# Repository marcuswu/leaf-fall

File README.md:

# Leaf Fall
Leaf Fall is a 6x3+4keys column-staggered split portable folding keyboard using Ultra-Low Profile (ULP) switches which builds on the Leaf Fold to add it to the unwired family tree ([Lotus 58 unWired](https://www.reddit.com/r/ErgoMechKeyboards/comments/1h69vc7/ad_lotus_58_unwired_available_for_preorder/), [Mitosis](https://www.reddit.com/r/MechanicalKeyboards/comments/66588f/wireless_split_qmk_mitosis/), and [mikefives](https://www.reddit.com/r/ErgoMechKeyboards/comments/1qfprec/mikefives_split_incl_my_longest_writeup_ever/))

## Warning ##
This board is under active development and is not ready for builds yet. In particular, some of the models, the bill of materials, etc are not up to date.

## Introduction and Background

During the planning phase for my ULP switches, [u/dynam1keNL](https://www.reddit.com/user/dynam1keNL/) posted about his mikefives, a radical new build that was diodeless, wireless, portless, and ultra-low power due to use of the Nordic Gazell wireless protocol among other innovations.

The ultra-low power design had me entralled and I knew I had to make a version of my Leaf Fold that builds in some of those features. This became the Leaf Fall.

## Using this repository

This repository contains:

* Models for the keyboard's case in STEP format with engineering drawings
* KiCAD project for the PCB

A [bill of materials](https://docs.google.com/spreadsheets/d/1gnvod9HGQc0NwxPJ2fzenmY7mPNX9EfSASZGwRChprs/edit?gid=0#gid=0) for constructing the keyboard is also available

## Build Guide

A build guide is in the works.

## TODO

* Update the board to remove ports, power switch, reset button
* Update Case to remove holes for ports, power switch, reset button
* Remove diodes
* Design dongle
* Ensure new ULP switches work
* Build it & test it
* Create a build guide
* Update the BoM (build it into this repo so it is versioned)

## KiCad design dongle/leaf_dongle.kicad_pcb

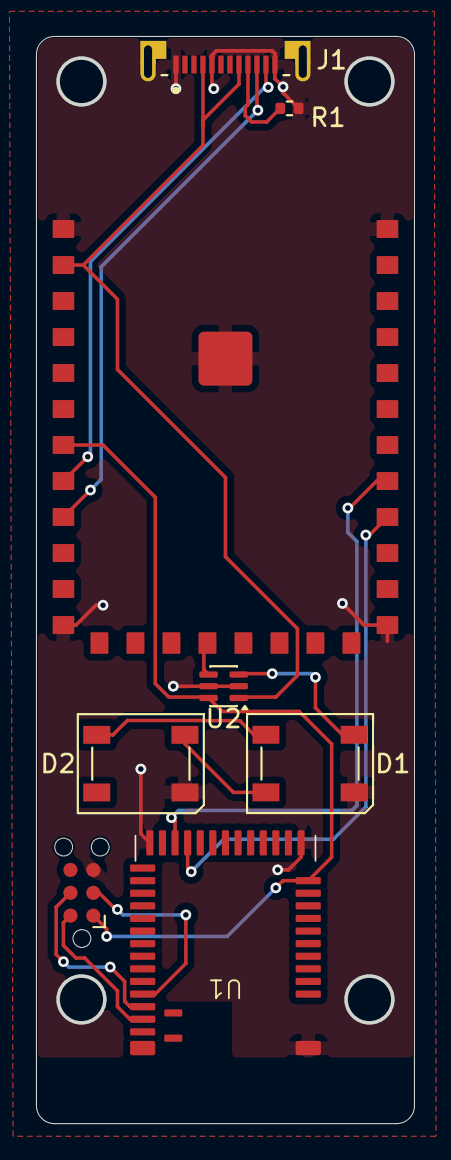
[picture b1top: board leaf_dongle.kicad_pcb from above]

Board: 2 copper layers, 20.9 x 60.3 mm, 8 parts (0 on the bottom side), 15 nets.

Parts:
1: MODULE_RP2040_SHIELD
D1, D2: SK6812; LED_SK6812_PLCC4_5.0x5.0mm_P3.2mm
J1: UP20-C-F-G-FL-P12-TR; SAMESKY_UP20-C-F-G-FL-P12-TR
J2: TC2030; Tag-Connect_TC2030-IDC-NL_2x03_P1.27mm_Vertical
R1: 5.1k; R_0402_1005Metric
U1: Raytac_MDBT42Q_P
U2: SN74LVC1T45DCK; SOT-363_SC-70-6

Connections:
-3V3: 1.7 (3V3), J2.1, U1.11 (VDD), U2.6 (VCCB)
GND: 1.1 (GND), 1.12 (GND), 1.21 (GND), 1.32 (GND), 1.33 (GND), D1.1 (VSS), D2.1 (VSS), J1.A1 (GND), J1.A12 (GND__1), J1.B12 (GND__2), J2.5, R1.2, U1.1 (GND), U1.12 (GND), U1.24 (GND), U2.2 (GND), U2.5 (DIR)
NEO: 1.16 (GP3), U2.4 (B)
unnamed: D1.2 (DIN), U2.3 (A)
unnamed: D1.4 (DOUT), D2.2 (DIN)
unnamed: D1.3 (VDD), D2.3 (VDD)
unnamed: J1.A5 (CC1), R1.1
RESET: J2.3, U1.35 (P0.21/RESET)
SWDCLK: J2.4, U1.36 (SWDCLK)
SWDIO: J2.2, U1.37 (SWDIO)
UART_RX: 1.25 (GP13), U1.22 (P0.09)
UART_TX: 1.24 (GP12), U1.21 (P0.08)
USB_D+: 1.9 (USB_D+), J1.A6 (DP1)
USB_D-: 1.8 (USB_D-), J1.A7 (DN1)
VCC: 1.2 (VIN), J1.A4 (VBUS), J1.B9 (VBUS__1), U2.1 (VCCA)

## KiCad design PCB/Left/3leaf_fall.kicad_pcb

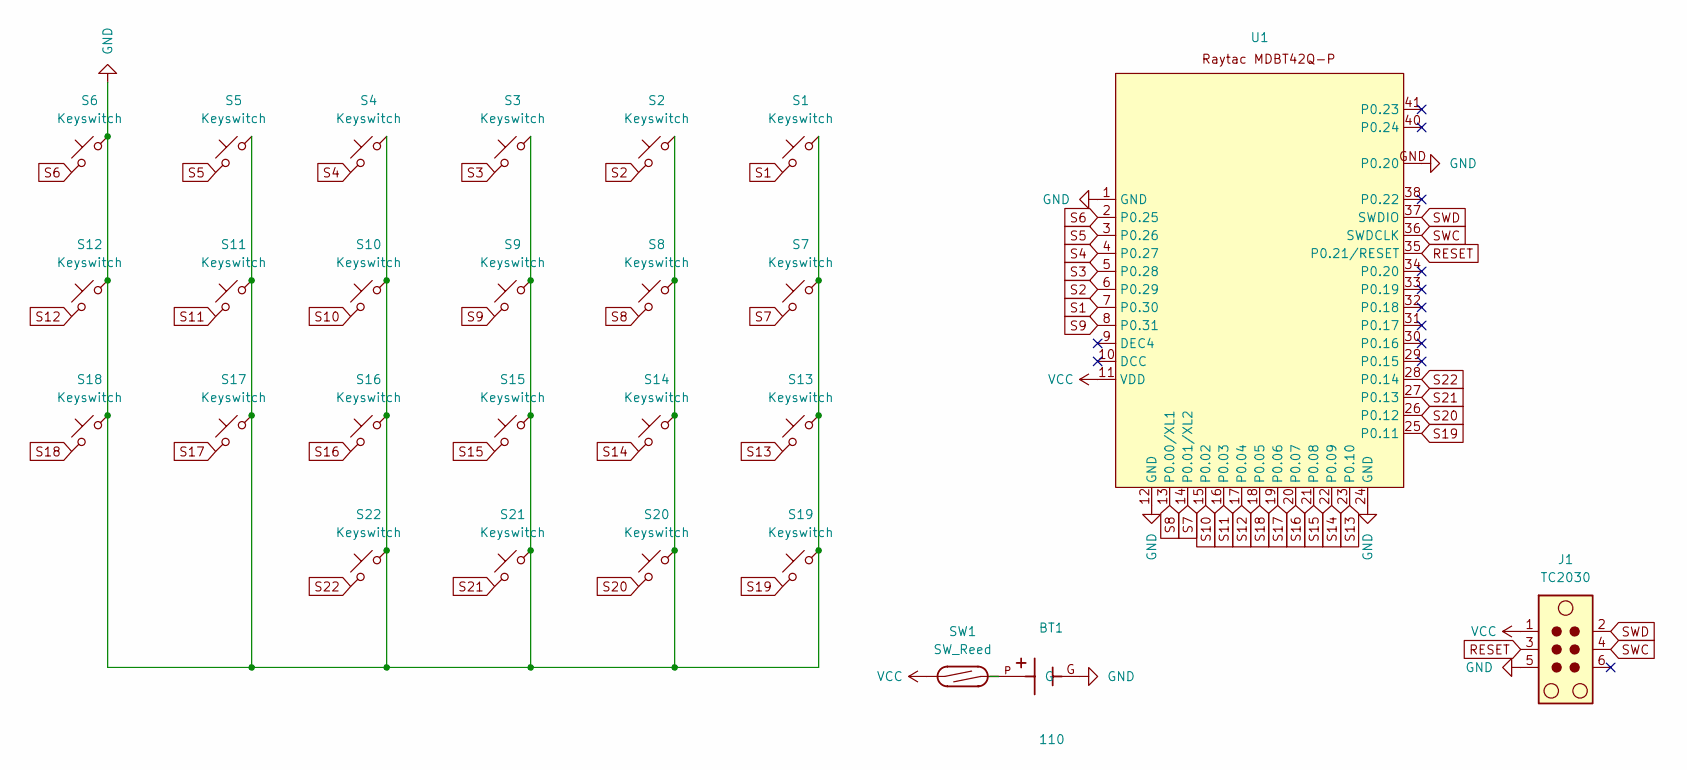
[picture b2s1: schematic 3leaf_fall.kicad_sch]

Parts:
BT1: 110; BAT_110_2032
J1: TC2030; Tag-Connect_TC2030-IDC-NL_2x03_P1.27mm_Vertical
S1, S2, S3, S4, S5, S6, S7, S8, S9, S10, S11, S12, S13, S14, S15, S16, S17, S18, S19, S20, S21, S22: Keyswitch; My_ULP_Scissor
SW1: SW_Reed; Magnet_reed_switch
U1: Raytac_MDBT42Q_P

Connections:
GND: BT1.G (G_G), J1.5, S1.1, S2.1, S3.1, S4.1, S5.1, S6.1, S7.1, S8.1, S9.1, S10.1, S11.1, S12.1, S13.1, S14.1, S15.1, S16.1, S17.1, S18.1, S19.1, S20.1, S21.1, S22.1, U1.1 (GND), U1.12 (GND), U1.24 (GND), U1.GND (P0.20)
unnamed: BT1.P, SW1.2
RESET: J1.3, U1.35 (P0.21/RESET)
S1: S1.2, U1.7 (P0.30)
S2: S2.2, U1.6 (P0.29)
S3: S3.2, U1.5 (P0.28)
S4: S4.2, U1.4 (P0.27)
S5: S5.2, U1.3 (P0.26)
S6: S6.2, U1.2 (P0.25)
S7: S7.2, U1.14 (P0.01/XL2)
S8: S8.2, U1.13 (P0.00/XL1)
S9: S9.2, U1.8 (P0.31)
S10: S10.2, U1.15 (P0.02)
S11: S11.2, U1.16 (P0.03)
S12: S12.2, U1.17 (P0.04)
S13: S13.2, U1.23 (P0.10)
S14: S14.2, U1.22 (P0.09)
S15: S15.2, U1.21 (P0.08)
S16: S16.2, U1.20 (P0.07)
S17: S17.2, U1.19 (P0.06)
S18: S18.2, U1.18 (P0.05)
S19: S19.2, U1.25 (P0.11)
S20: S20.2, U1.26 (P0.12)
S21: S21.2, U1.27 (P0.13)
S22: S22.2, U1.28 (P0.14)
SWC: J1.4, U1.36 (SWDCLK)
SWD: J1.2, U1.37 (SWDIO)
VCC: J1.1, SW1.1, U1.11 (VDD)

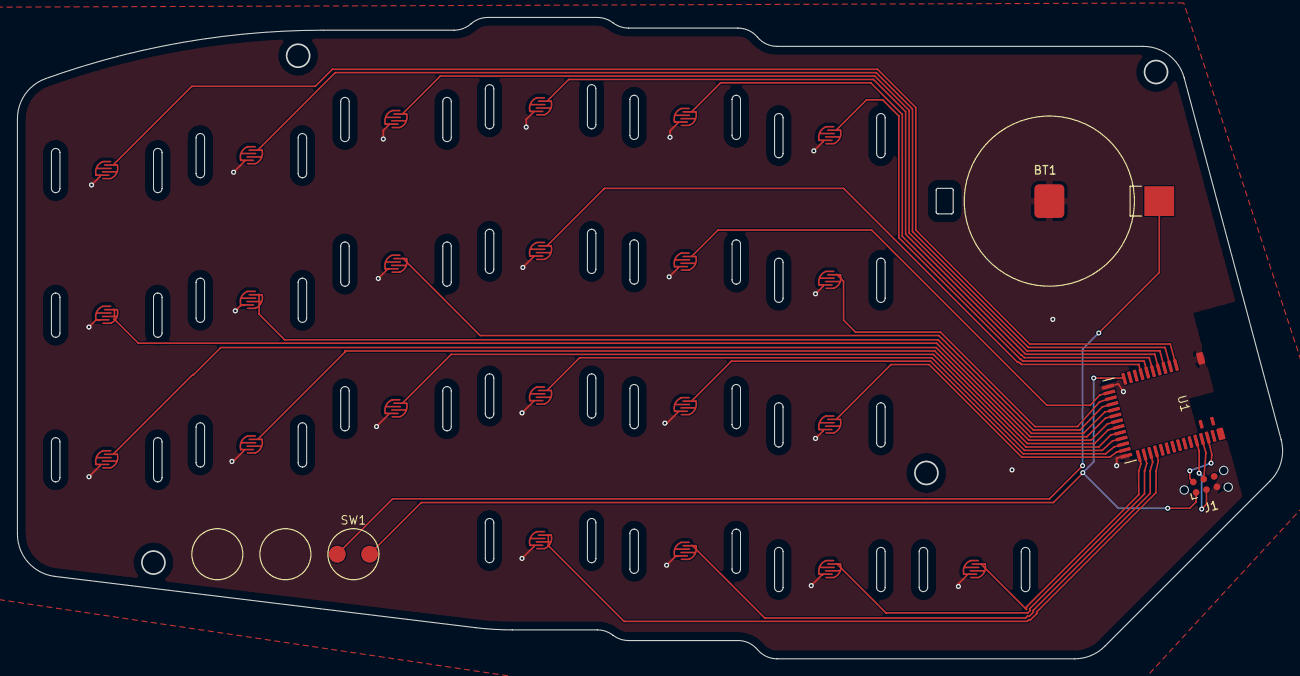
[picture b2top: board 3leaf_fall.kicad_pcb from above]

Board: 2 copper layers, 148.6 x 75.3 mm, 26 parts (0 on the bottom side), 28 nets.

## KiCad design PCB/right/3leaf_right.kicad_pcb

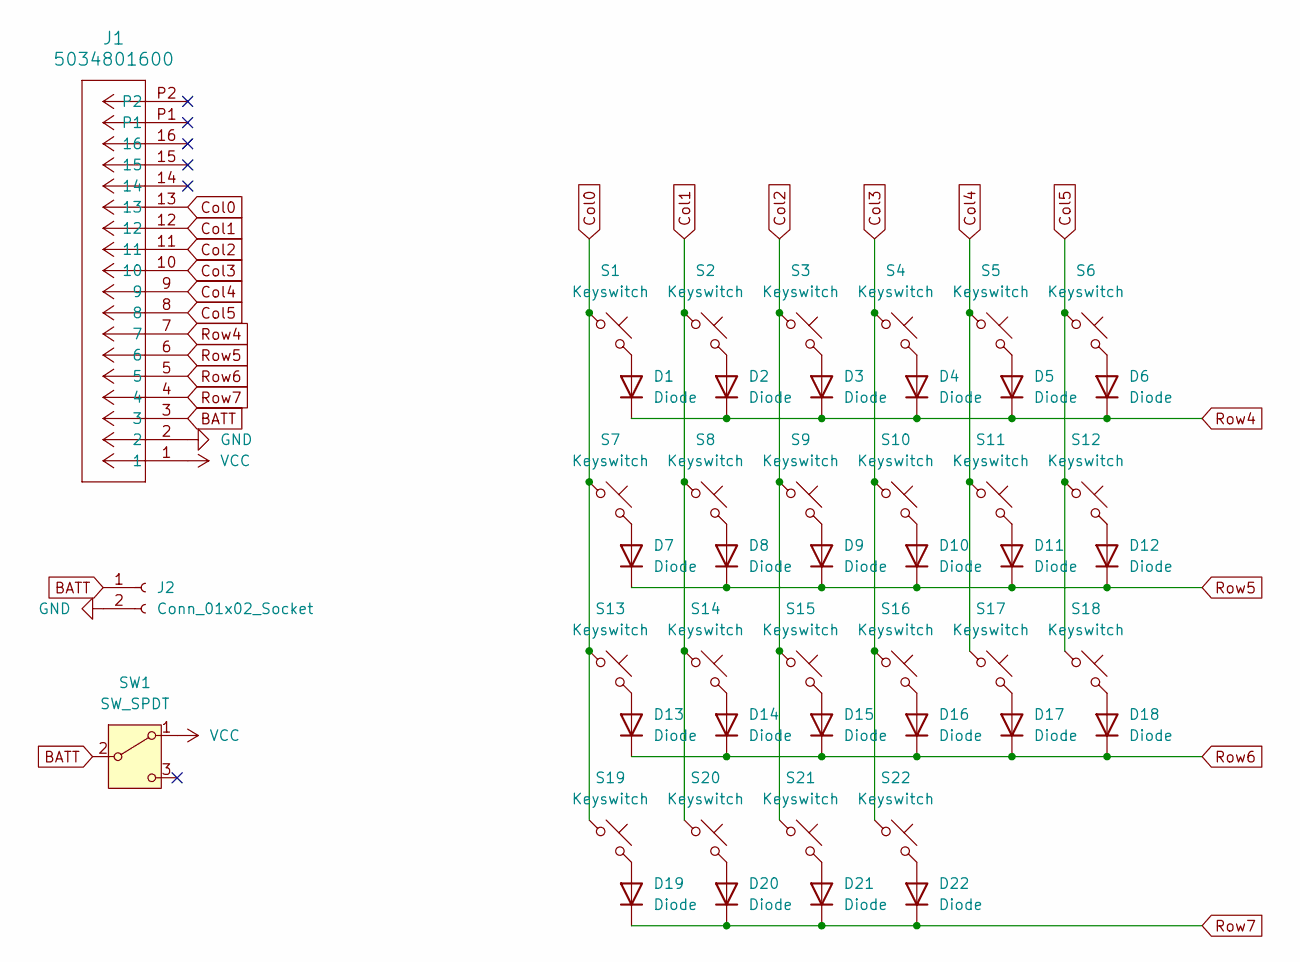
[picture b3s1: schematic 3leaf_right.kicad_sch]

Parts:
D1, D2, D3, D4, D5, D6, D7, D8, D9, D10, D11, D12, D13, D14, D15, D16, D17, D18, D19, D20, D21, D22: Diode; D_SOD-323
J1: 5034801600; CON_5034801600_MOL
J2: Conn_01x02_Socket; SM02B-SRSS-TB
S1, S2, S3, S4, S5, S6, S7, S8, S9, S10, S11, S12, S13, S14, S15, S16, S17, S18, S19, S20, S21, S22: Keyswitch; My_ULP_Scissor
SW1: SW_SPDT; Switch_MSK12C02

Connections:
BATT: J1.3, J2.1, SW1.2 (B)
Col0: J1.13, S1.1, S7.1, S13.1, S19.1
Col1: J1.12, S2.1, S8.1, S14.1, S20.1
Col2: J1.11, S3.1, S9.1, S15.1, S21.1
Col3: J1.10, S4.1, S10.1, S16.1, S22.1
Col4: J1.9, S5.1, S11.1, S17.1
Col5: J1.8, S6.1, S12.1, S18.1
GND: J1.2, J2.2
unnamed: D1.2 (A), S1.2
unnamed: D2.2 (A), S2.2
unnamed: D3.2 (A), S3.2
unnamed: D4.2 (A), S4.2
unnamed: D5.2 (A), S5.2
unnamed: D6.2 (A), S6.2
unnamed: D7.2 (A), S7.2
unnamed: D8.2 (A), S8.2
unnamed: D9.2 (A), S9.2
unnamed: D10.2 (A), S10.2
unnamed: D11.2 (A), S11.2
unnamed: D12.2 (A), S12.2
unnamed: D13.2 (A), S13.2
unnamed: D14.2 (A), S14.2
unnamed: D15.2 (A), S15.2
unnamed: D16.2 (A), S16.2
unnamed: D17.2 (A), S17.2
unnamed: D18.2 (A), S18.2
unnamed: D19.2 (A), S19.2
unnamed: D20.2 (A), S20.2
unnamed: D21.2 (A), S21.2
unnamed: D22.2 (A), S22.2
Row4: D1.1 (K), D2.1 (K), D3.1 (K), D4.1 (K), D5.1 (K), D6.1 (K), J1.7
Row5: D7.1 (K), D8.1 (K), D9.1 (K), D10.1 (K), D11.1 (K), D12.1 (K), J1.6
Row6: D13.1 (K), D14.1 (K), D15.1 (K), D16.1 (K), D17.1 (K), D18.1 (K), J1.5
Row7: D19.1 (K), D20.1 (K), D21.1 (K), D22.1 (K), J1.4
VCC: J1.1, SW1.1 (A)

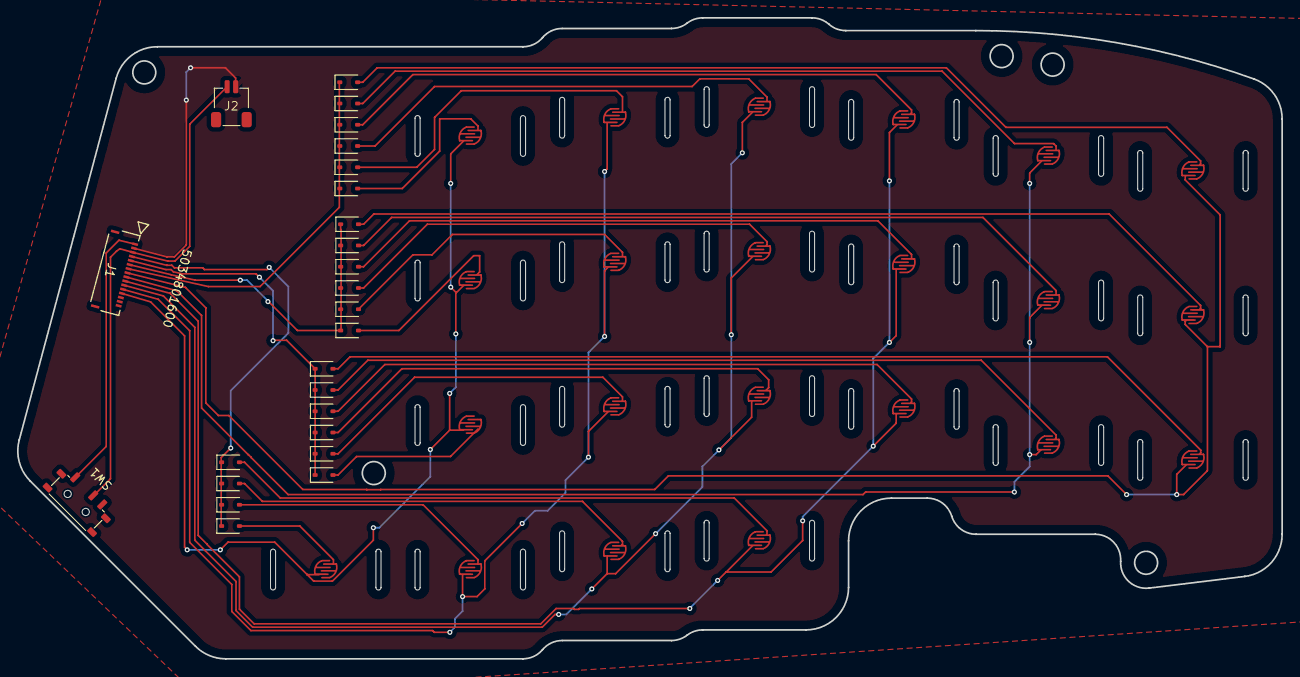
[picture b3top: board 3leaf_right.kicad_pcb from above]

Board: 2 copper layers, 148.7 x 75.4 mm, 47 parts (0 on the bottom side), 35 nets.

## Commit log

2026-03-27 Initial commit -- basically a copy of Leaf Fold
2026-03-27 Set up for reversible PCB
2026-04-02 Near completion
    * Updated switch footprint to meet PCB fab reqs
    * Chose Raytac MDBT42 MCU
    * Removed diodes
    * Updated traces for diodeless config
    * Added CR2032 battery contacts
    * Removed USB board cutout
2026-04-11 Add initial firmware, dongle
2026-04-11 Set up for left and right PCB designs
2026-04-15 Add TC-2030 interface; generate gerbers
2026-04-16 left/right configs; low power warning
2026-04-16 fix button assignments
2026-04-16 use inlines for performance; update comments
2026-04-18 Small fixes
    * Fix column order in uart data to make it easier for qmk firmware
    * Fix updating previous button states in keyboard firmware
2026-04-20 Big rework initially started to add debouncing
    * Use RTC to schedule our key polling and inactivity checks
    * Handle debounce as part of key polling
    * Use GPIOTE sense to be alerted of activity for exiting sleep
    * Read all GPIO key states at once
    * A lot of refactoring for single responsibility
2026-04-24 Use env for keyboard side selection
2026-04-24 Update step files
2026-04-24 Add initial pass at CI
2026-04-24 move github ci to proper path
2026-04-24 fix inability to find nrfutil
2026-04-24 add progress logs to toolchain/sdk setup
2026-04-24 more logging
2026-04-24 fixed a path; more debugging
2026-04-25 Update CI workflow to show environment variables
    Changed 'pwd' command to 'env' to display environment variables.
2026-04-25 Debug contents of ncs install
2026-04-27 Use logic shifter on dongle
2026-05-15 fix rtt and gpiote init
2026-05-16 Both RTC handlers are now working
2026-05-16 use rtc1 for both keepalive and debounce
2026-05-16 fix paths in west build command
2026-05-16 add echos for command for debugging ci
2026-05-16 fix paths based on echoed west command
2026-05-16 fix paths again -h forgot to make the regex global
2026-05-16 what west are we running
2026-05-16 set zephyr_base
2026-05-18 Many fixes -- gpio still not reading correctly
2026-05-18 remove CI...
2026-05-18 remove unused code, clear up read keys
2026-05-18 some cleanup
2026-05-20 use nfc and reset pins as gpios
2026-05-26 Update raytac module devicetree to allow for all 3 of the SoCs it can have
2026-06-02 Fix gpio reads by moving from rtc to counter
2026-06-03 Update dongle to have 5.1k resistor for USB power
2026-06-12 working keyboard devices
2026-06-12 Fix dongle gazell and uart
2026-06-26 Fix left keyboard gpio mapping, dongle key state transfer
